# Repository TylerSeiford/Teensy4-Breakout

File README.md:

# Teensy4-Breakout
 Uno style breakout for Teensy4.0

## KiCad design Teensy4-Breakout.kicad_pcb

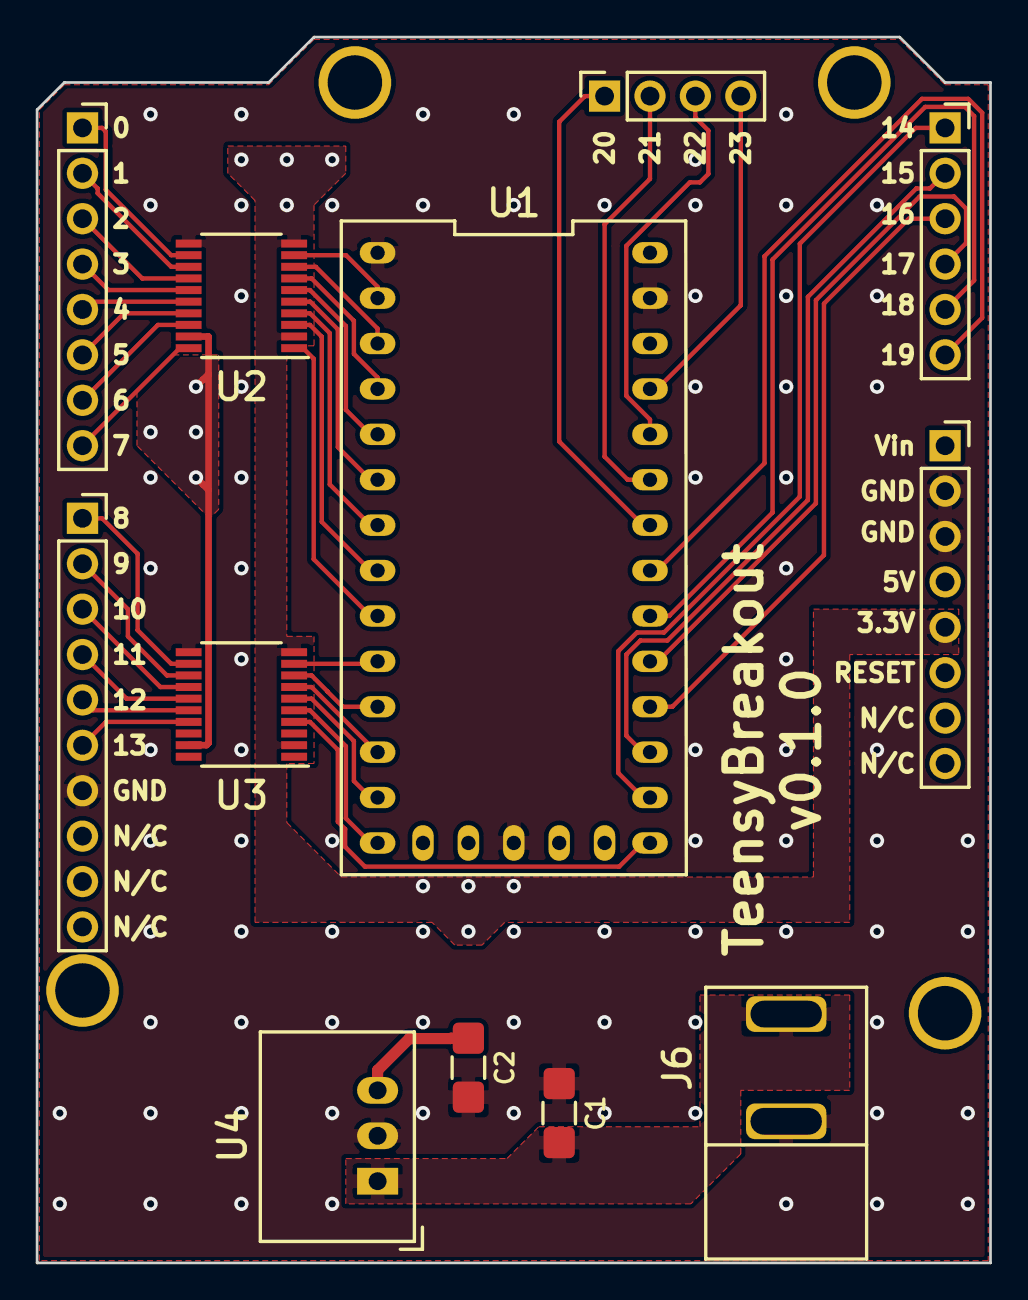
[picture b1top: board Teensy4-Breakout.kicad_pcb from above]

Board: 2 copper layers, 53.3 x 68.6 mm, 16 parts (0 on the bottom side), 42 nets.

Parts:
C1, C2: 10uF; C_1206_3216Metric_Pad1.42x1.75mm_HandSolder
H1, H2, H3, H4: MountingHole; Hole
J1: DIO 0-7; J1
J2: DIO 8-13, GND, NC x 3; J2
J3: AI 6-9/DIO 20-23; J3
J4: AI 0-5/DIO 14-19; J4
J5: PWR; J5
J6: Barrel_Jack; PJ-037A
U1: Teensy4.0
U2, U3: TXB0108PWR; TSSOP-20_4.4x6.5mm_P0.65mm
U4: R-78E5.0-1.0; Converter_DCDC_RECOM_R-78E-1.0_THT

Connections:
/0-3.3: U1.2, U2.9
/0-5.0: J1.1, U2.12
/1-3.3: U1.3, U2.8
/1-5.0: J1.2, U2.13
/2-3.3: U1.4, U2.7
/2-5.0: J1.3, U2.14
/3-3.3: U1.5, U2.6
/3-5.0: J1.4, U2.15
/3.3V: J5.5, U1.16, U1.31, U2.2, U2.10, U3.2, U3.10
/4-3.3: U1.6, U2.5
/4-5.0: J1.5, U2.16
/5-3.3: U1.7, U2.4
/5-5.0: J1.6, U2.17
/5V: C2.1, J5.4, U1.33, U2.19, U3.19, U4.3
/6-3.3: U1.8, U2.3
/6-5.0: J1.7, U2.18
/7-3.3: U1.9, U2.1
/7-5.0: J1.8, U2.20
/8-3.3: U1.10, U3.9
/8-5.0: J2.1, U3.12
/9-3.3: U1.11, U3.8
/9-5.0: J2.2, U3.13
/10-3.3: U1.12, U3.7
/10-5.0: J2.3, U3.14
/11-3.3: U1.13, U3.6
/11-5.0: J2.4, U3.15
/12-3.3: U1.14, U3.5
/12-5.0: J2.5, U3.16
/13-3.3: U1.20, U3.4
/13-5.0: J2.6, U3.17
/14-3.3: J4.1, U1.21
/15-3.3: J4.2, U1.22
/16-3.3: J4.3, U1.23
/17-3.3: J4.4, U1.24
/18-3.3: J4.5, U1.25
/19-3.3: J4.6, U1.26
/20-3.3: J3.1, U1.27
/21-3.3: J3.2, U1.28
/22-3.3: J3.3, U1.29
/23-3.3: J3.4, U1.30
/GND: C1.1, C2.2, J2.7, J5.2, J5.3, J6.2, U1.1, U1.17, U1.32, U2.11, U3.11, U4.2
/Vin: C1.2, J5.1, J6.1, U4.1

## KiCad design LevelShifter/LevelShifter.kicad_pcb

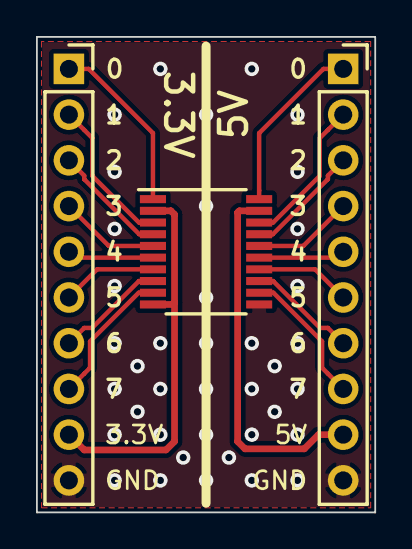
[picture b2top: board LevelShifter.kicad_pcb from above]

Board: 2 copper layers, 18.8 x 26.4 mm, 3 parts (0 on the bottom side), 19 nets.

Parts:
J1, J2: Conn_01x10_Male; PinSocket_1x10_P2.54mm_Vertical
U1: TXB0108PWR; TSSOP-20_4.4x6.5mm_P0.65mm

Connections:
/0-3.3V: J2.1, U1.1
/0-5V: J1.1, U1.20
/1-3.3V: J2.2, U1.3
/1-5V: J1.2, U1.18
/2-3.3V: J2.3, U1.4
/2-5V: J1.3, U1.17
/3-3.3V: J2.4, U1.5
/3-5V: J1.4, U1.16
/3.3V: J2.9, U1.2, U1.10
/4-3.3V: J2.5, U1.6
/4-5V: J1.5, U1.15
/5-3.3V: J2.6, U1.7
/5-5V: J1.6, U1.14
/5V: J1.9, U1.19
/6-3.3V: J2.7, U1.8
/6-5V: J1.7, U1.13
/7-3.3V: J2.8, U1.9
/7-5V: J1.8, U1.12
/GND: J1.10, J2.10, U1.11

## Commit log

2019-10-01 Initial upload
2019-10-01 Fixed analog pins, switched right side to 3.3V
    V0.0.2
2019-10-13 Cleaned up traces, fixed 3.3V plane and final checks
    PCB v0.0.3
2019-10-13 Final cleanup, capacitor footprint increase
    PCB v0.0.4
2019-11-09 PCB rev 0.1.0
2019-11-09 Missed a few things
2019-11-09 Prototype Level Shifter v0.1.0
2019-11-09 Updates to header sizes
